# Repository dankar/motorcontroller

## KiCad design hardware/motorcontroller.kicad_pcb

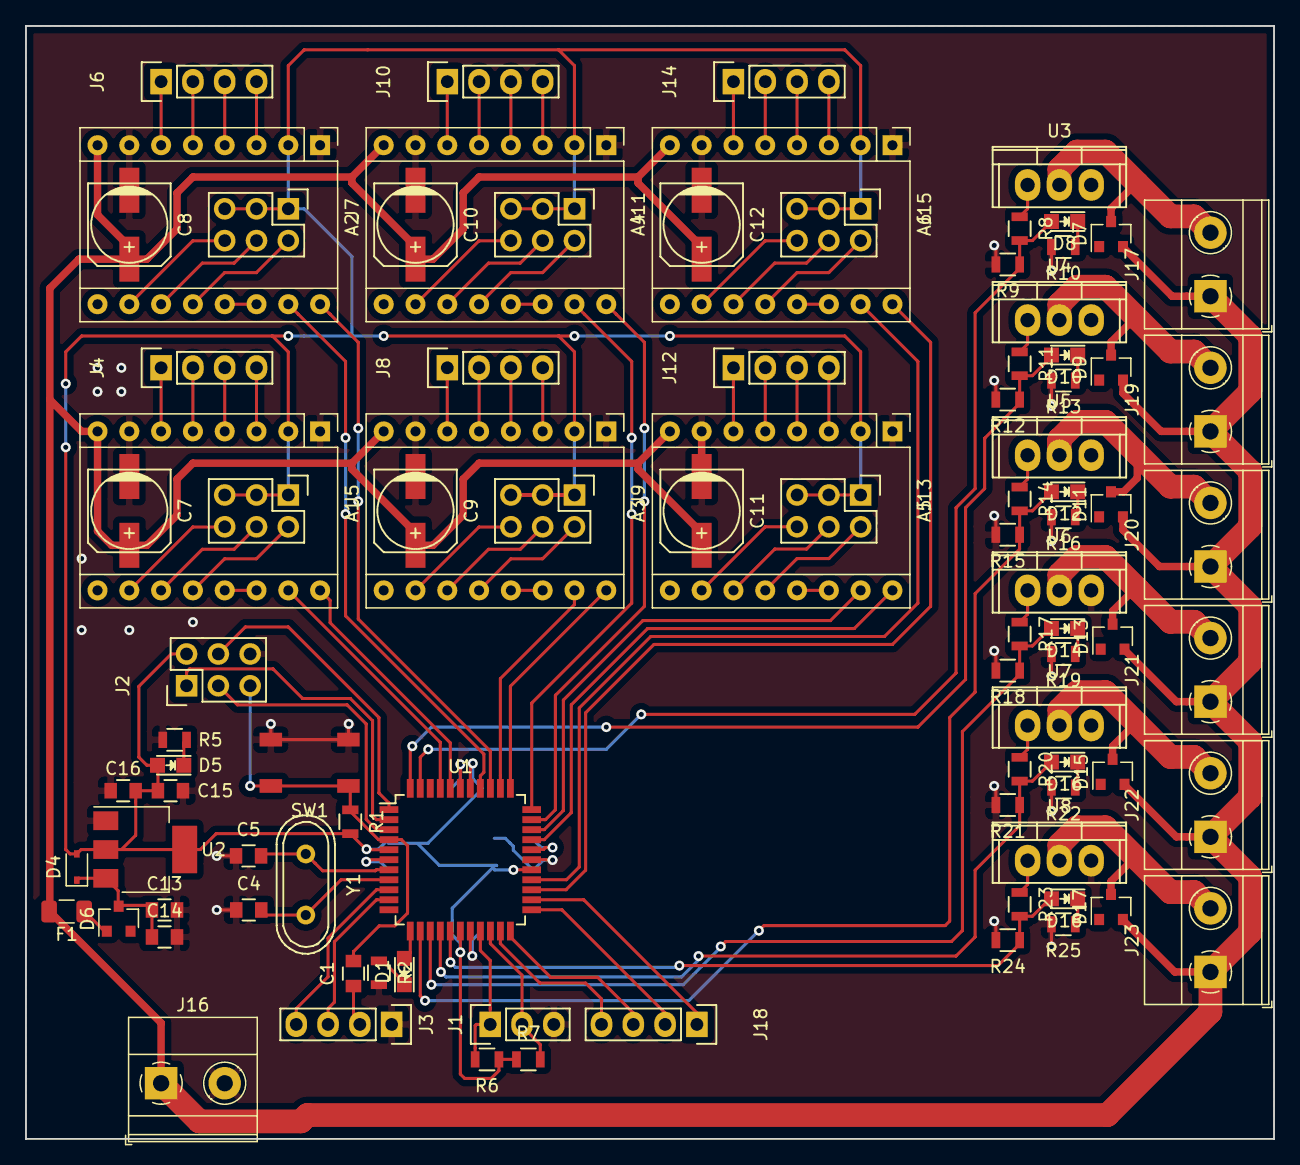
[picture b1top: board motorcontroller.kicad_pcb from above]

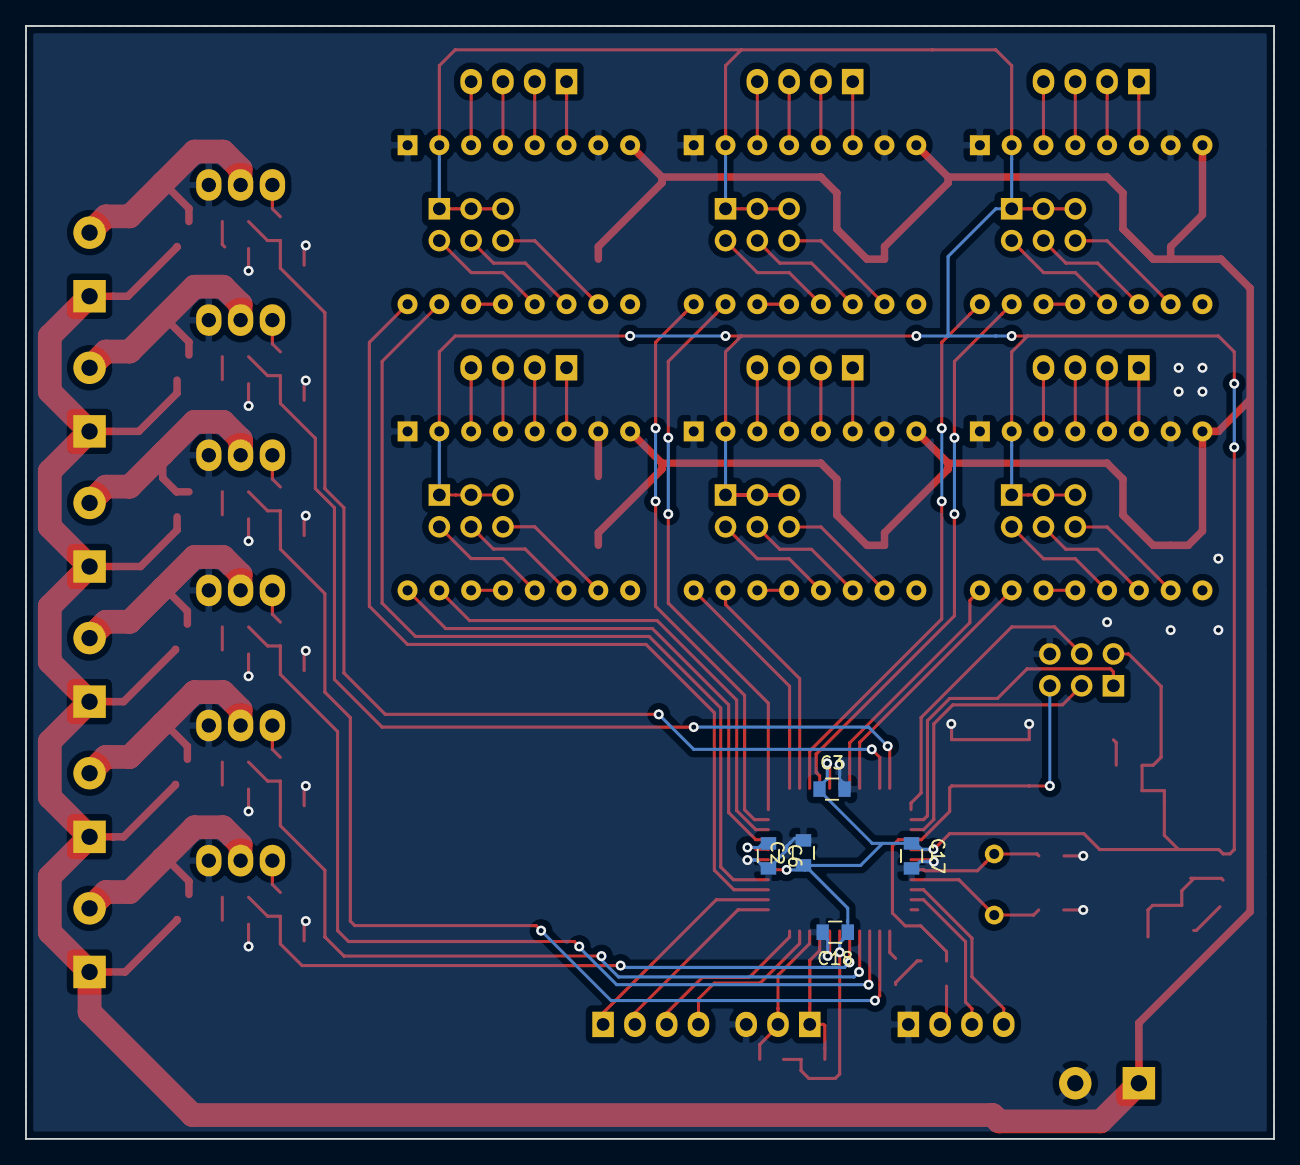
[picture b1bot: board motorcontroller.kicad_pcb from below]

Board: 2 copper layers, 99.7 x 88.9 mm, 97 parts (5 on the bottom side), 108 nets.

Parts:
A1, A2, A3, A4, A5, A6: Pololu_Breakout_A4988; Pololu_Breakout-16_15.2x20.3mm
C1, C2, C3, C6, C14, C16, C17, C18: 100n; C_0805
C4, C5: 22p; C_0805
C7, C8, C9, C10, C11, C12: CP; c_elec_6.3x5.3
C13, C15: 10u; C_0805
D1: Status 1; LED_0805
D4: 1n4148; D_SOD-323
D5: 3.3V PWR; LED_0805
D6: BAT54C; SOT-23
D7, D9, D11, D13, D15, D17: BAV99; SOT-23
D8, D10, D12, D14, D16, D18: LED; LED_0805
F1: 0.25A; Fuse_1206_3216Metric
J1: UART Header; Pin_Header_Straight_1x04
J2: SPI Header; Pin_Header_Straight_2x03
J3: I2C Header; Pin_Header_Straight_1x03
J4, J6, J8, J10, J12, J14, J18: Conn_01x04_Male; Pin_Header_Straight_1x04
J5, J7, J9, J11, J13, J15: Conn_02x03_Counter_Clockwise; Pin_Header_Straight_2x03
J16, J17, J19, J20, J21, J22, J23: Screw_Terminal_01x02; TerminalBlock_Phoenix_MKDS-1,5-2-5.08_1x02_P5.08mm_Horizont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
R1: 10k; R_0805
R2, R5, R10, R13, R16, R19, R22, R25: 200; R_0805
R6, R7: 4k7; R_0805
R8, R11, R14, R17, R20, R23: 10; R_0805
R9, R12, R15, R18, R21, R24: 100k; R_0805
SW1: Reset; Switch
U1: ATmega1284P-AU; TQFP-44_10x10mm_Pitch0.8mm
U2: TLV1117-33; SOT-223-3_TabPin2
U3, U4, U5, U6, U7, U8: STP55NF06L; TO-220
Y1: 16MHz; Crystal_HC49-U_Vertical

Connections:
+3V3: A1.2, A2.2, A3.2, A4.2, A5.2, A6.2, C2.1, C3.1, C15.1, C16.1, C17.1, C18.1, D4.2, D5.2, J2.2, J5.1, J5.3, J5.5, J7.1, J7.3, J7.5, J9.1, J9.3, J9.5, J11.1, J11.3, J11.5, J13.1, J13.3, J13.5, J15.1, J15.3, J15.5, R1.2, R6.1, R7.1, U1.5, U1.17, U1.27, U1.38, U2.2
+12V: A1.8, A2.8, A3.8, A4.8, A5.8, A6.8, C7.1, C8.1, C9.1, C10.1, C11.1, C12.1, D7.2, D9.2, D11.2, D13.2, D15.2, D17.2, F1.2, J16.1, J17.1, J19.1, J20.1, J21.1, J22.1, J23.1
/MCU/AREF: C6.1, U1.29
/MCU/DTR: C1.1, J1.2
/MCU/GPIO_1: J18.4, U1.21
/MCU/GPIO_2: J18.3, U1.22
/MCU/GPIO_3: J18.2, U1.23
/MCU/GPIO_4: J18.1, U1.24
/MCU/MISO: J2.1, U1.2
/MCU/MOSI: J2.4, U1.1
/MCU/SCK: J2.3, U1.3
/MCU/UART_RX: J1.4, U1.9
/MCU/UART_TX: J1.3, U1.10
DIR_1: A1.16, U1.40
DIR_2: A2.16, U1.36
DIR_3: A3.16, U1.34
DIR_4: A4.16, U1.32
DIR_5: A5.16, U1.30
DIR_6: A6.16, U1.25
FET_1: D8.2, R8.2, R9.1, U1.43
FET_2: D10.2, R11.2, R12.1, U1.44
FET_3: D12.2, R14.2, R15.1, U1.13
FET_4: D14.2, R17.2, R18.1, U1.14
FET_5: D16.2, R20.2, R21.1, U1.15
FET_6: D18.2, R23.2, R24.1, U1.16
GND: A1.1, A1.7, A2.1, A2.7, A3.1, A3.7, A4.1, A4.7, A5.1, A5.7, A6.1, A6.7, C2.2, C3.2, C4.1, C5.1, C6.2, C7.2, C8.2, C9.2, C10.2, C11.2, C12.2, C13.2, C14.2, C15.2, C16.2, C17.2, C18.2, J1.1, J2.6, J3.3, J16.2, R2.2, R5.2, R9.2, R10.2, R12.2, R13.2, R15.2, R16.2, R18.2, R19.2, R21.2, R22.2, R24.2, R25.2, SW1.2, U1.6, U1.18, U1.28, U1.39, U2.1, U3.3, U4.3, U5.3, U6.3, U7.3, U8.3
unnamed: A1.3, J4.4
unnamed: A1.4, J4.3
unnamed: A1.5, J4.2
unnamed: A1.6, J4.1
unnamed: A1.10, J5.6
unnamed: A1.11, J5.4
unnamed: A1.12, J5.2
unnamed: A1.13, A1.14
unnamed: A2.3, J6.4
unnamed: A2.4, J6.3
unnamed: A2.5, J6.2
unnamed: A2.6, J6.1
unnamed: A2.10, J7.6
unnamed: A2.11, J7.4
unnamed: A2.12, J7.2
unnamed: A2.13, A2.14
unnamed: A3.3, J8.4
unnamed: A3.4, J8.3
unnamed: A3.5, J8.2
unnamed: A3.6, J8.1
unnamed: A3.10, J9.6
unnamed: A3.11, J9.4
unnamed: A3.12, J9.2
unnamed: A3.13, A3.14
unnamed: A4.3, J10.4
unnamed: A4.4, J10.3
unnamed: A4.5, J10.2
unnamed: A4.6, J10.1
unnamed: A4.10, J11.6
unnamed: A4.11, J11.4
unnamed: A4.12, J11.2
unnamed: A4.13, A4.14
unnamed: A5.3, J12.4
unnamed: A5.4, J12.3
unnamed: A5.5, J12.2
unnamed: A5.6, J12.1
unnamed: A5.10, J13.6
unnamed: A5.11, J13.4
unnamed: A5.12, J13.2
unnamed: A5.13, A5.14
unnamed: A6.3, J14.4
unnamed: A6.4, J14.3
unnamed: A6.5, J14.2
unnamed: A6.6, J14.1
unnamed: A6.10, J15.6
unnamed: A6.11, J15.4
unnamed: A6.12, J15.2
unnamed: A6.13, A6.14
unnamed: C4.2, U1.8, Y1.2
unnamed: C5.2, U1.7, Y1.1
unnamed: C13.1, C14.1, D4.1, D6.3, U2.3
unnamed: D1.1, R2.1
unnamed: D5.1, R5.1
unnamed: D6.1, F1.1
unnamed: D7.3, J17.2, U3.2
unnamed: D8.1, R10.1
unnamed: D9.3, J19.2, U4.2
unnamed: D10.1, R13.1
unnamed: D11.3, J20.2, U5.2
unnamed: D12.1, R16.1
unnamed: D13.3, J21.2, U6.2
unnamed: D14.1, R19.1
unnamed: D15.3, J22.2, U7.2
unnamed: D16.1, R22.1
unnamed: D17.3, J23.2, U8.2
unnamed: D18.1, R25.1
unnamed: R8.1, U3.1
unnamed: R11.1, U4.1
unnamed: R14.1, U5.1
unnamed: R17.1, U6.1
unnamed: R20.1, U7.1
unnamed: R23.1, U8.1
RESET: C1.2, J2.5, R1.1, SW1.1, U1.4
SCL: J3.1, R6.2, U1.19
SDA: J3.2, R7.2, U1.20
STATUS_1: D1.2, U1.12
STEP_1: A1.15, U1.41
STEP_2: A2.15, U1.37
STEP_3: A3.15, U1.35
STEP_4: A4.15, U1.33
STEP_5: A5.15, U1.31
STEP_6: A6.15, U1.26

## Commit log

2020-04-20 Cleanup
2020-04-20 Added image
